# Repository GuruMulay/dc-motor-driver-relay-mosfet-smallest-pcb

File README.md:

View this project on [CADLAB.io](https://cadlab.io/project/1370).

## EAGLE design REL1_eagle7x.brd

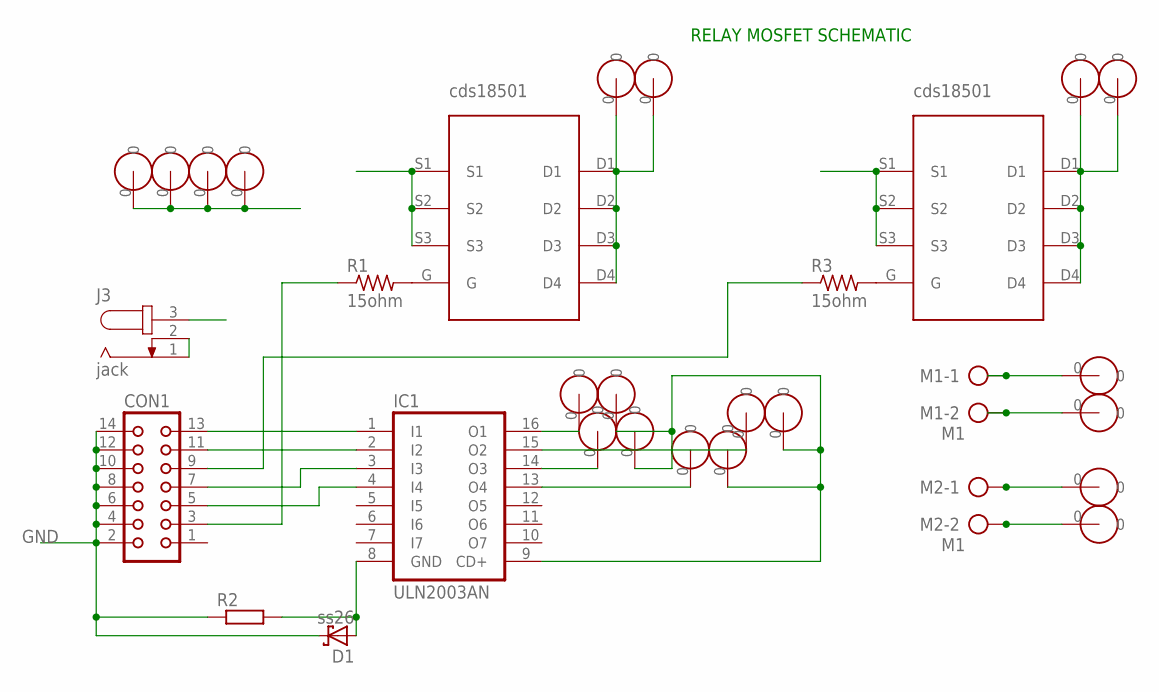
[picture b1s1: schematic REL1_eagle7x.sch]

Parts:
24V: PAD0; SWITCHPAD
CON1: CON14
D1: ss26; SMB
IC1: ULN2003AN; DIL16
J3: jack; SPC4077
M1, M2: M1; AK300/2
R1, R3: 15ohm; M1206
R2: R-EU_0414/15; 0414/15
U$1, U$2, U$3, U$4, U$5, U$6, U$7, U$8, U$9, U$10, U$13, U$14, U$15, U$16, U$17, U$18, U$19, U$20, U$21: PAD0; SWITCHPAD
U$11, U$12: CSD18503GDS-NEW; CDS

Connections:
24V: 24V.0, IC1.9 (CD+), J3.3, U$3.0, U$4.0, U$6.0, U$8.0, U$9.0, U$10.0, U$21.0
GND: CON1.2, CON1.4, CON1.6, CON1.8, CON1.10, CON1.12, CON1.14, D1.C, J3.1, J3.2, R2.1, U$11.S1, U$11.S2, U$11.S3, U$12.S1, U$12.S2, U$12.S3
unnamed: IC1.16 (O1), U$1.0
unnamed: CON1.5, IC1.4 (I4)
unnamed: IC1.14 (O3), U$5.0
unnamed: CON1.7, IC1.3 (I3)
unnamed: IC1.13 (O4), U$7.0
unnamed: CON1.11, IC1.2 (I2)
unnamed: CON1.13, IC1.1 (I1)
unnamed: IC1.15 (O2), U$2.0
unnamed: R1.2, U$11.G
unnamed: R3.2, U$12.G
unnamed: CON1.3, R1.1
unnamed: CON1.9, R3.1
unnamed: U$11.D1, U$11.D2, U$11.D3, U$11.D4, U$13.0, U$15.0
unnamed: D1.A, IC1.8 (GND), R2.2
unnamed: U$12.D1, U$12.D2, U$12.D3, U$12.D4, U$14.0, U$16.0
unnamed: M1.2, U$18.0
unnamed: M1.1, U$17.0
unnamed: M2.1, U$19.0
unnamed: M2.2, U$20.0

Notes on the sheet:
RELAY MOSFET SCHEMATIC

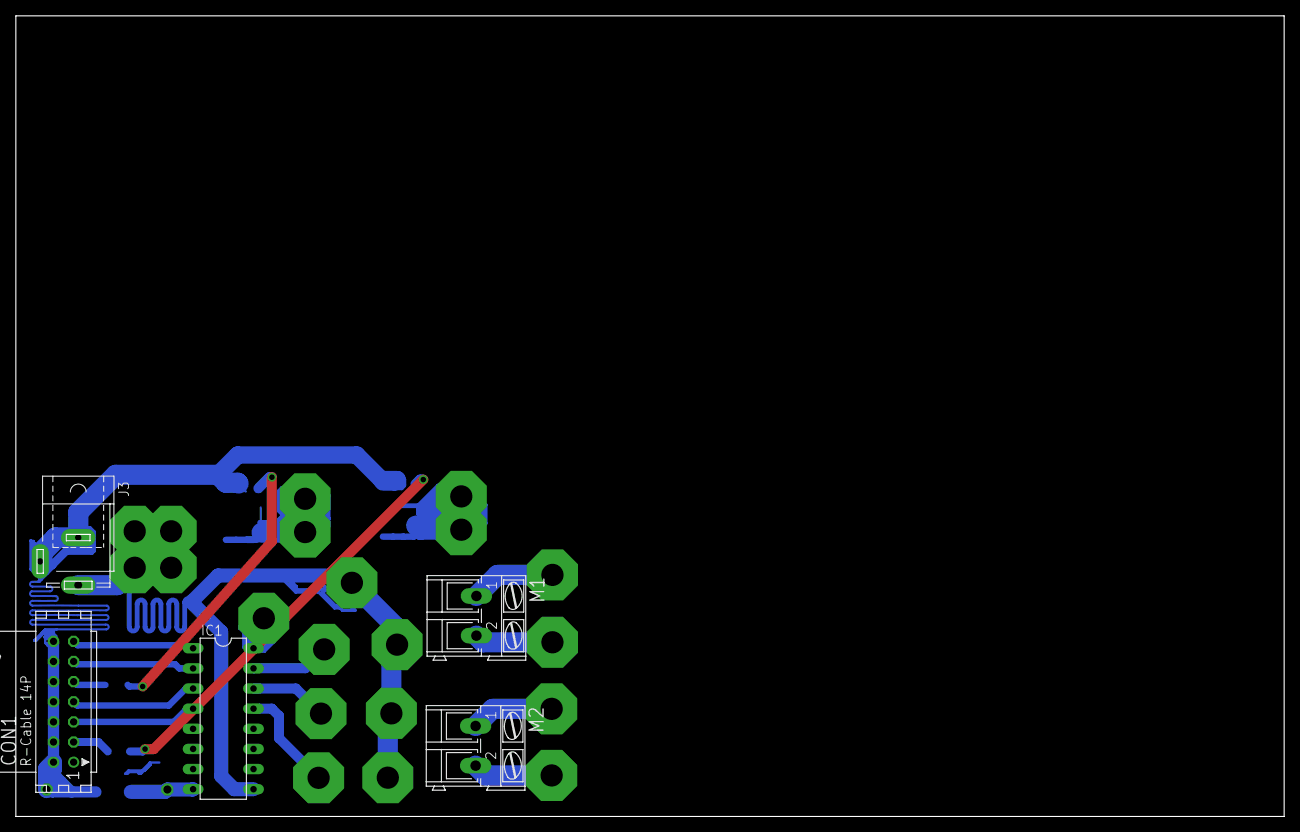
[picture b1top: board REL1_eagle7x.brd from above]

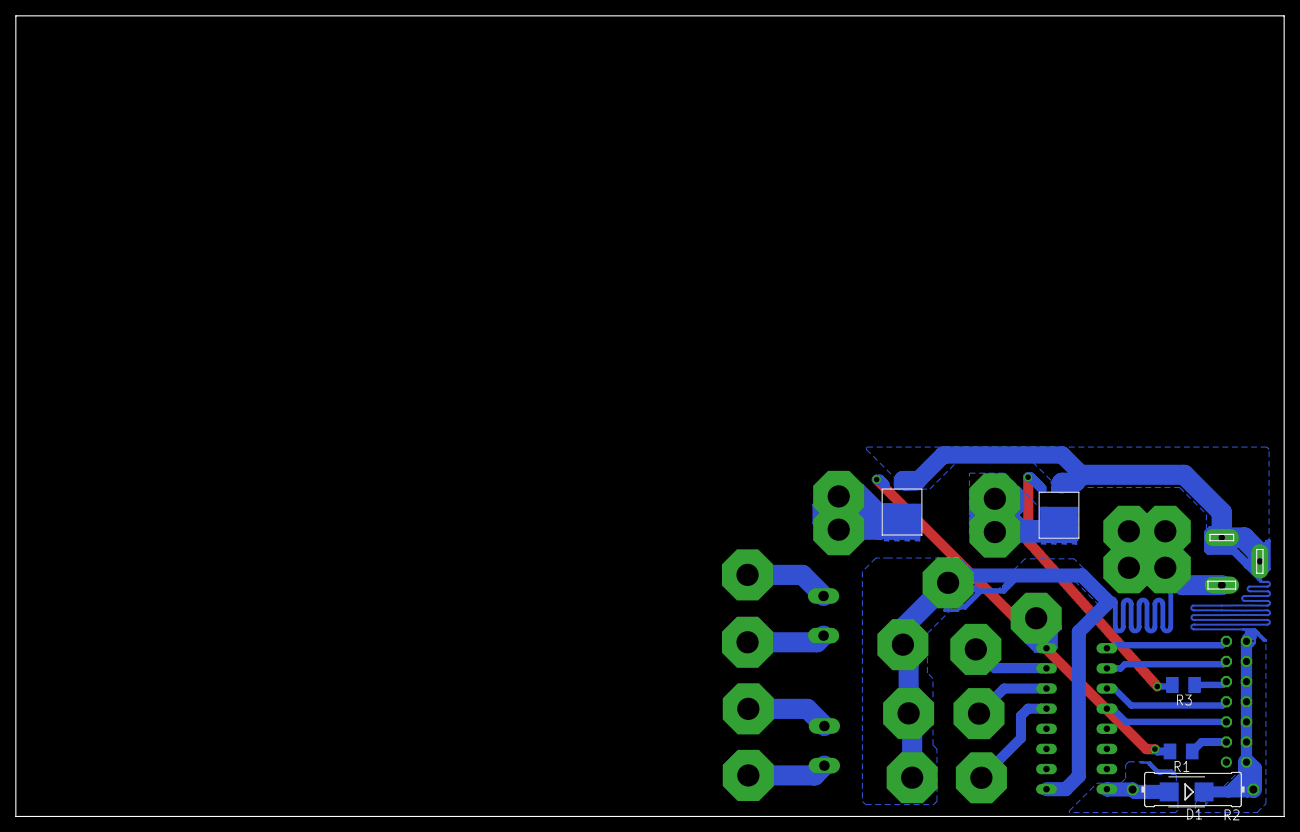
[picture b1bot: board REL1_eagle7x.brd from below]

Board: 2 copper layers, 160.0 x 101.0 mm, 31 parts (6 on the bottom side), 21 nets.

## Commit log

2018-10-13 Init proj relay mosfet smd smallest
2018-10-13 Add images
2018-10-13 Add pdfs of board and schematics
2018-10-13 Add .brd and .sch files
2018-10-13 Backlink to CADLAB.io has been added.
2018-11-11 Add hands-on testing images
